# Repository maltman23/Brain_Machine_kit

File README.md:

# Brain Machine Kit  
  
A hackable Sound &amp; Light Machine kit that is easy to make,  
&nbsp;&nbsp;&nbsp;&nbsp;&nbsp;&nbsp;&nbsp;and comes pre-programmed with a really nice 14-minute meditation brainwave sequence.  
Not only that, but you get to hallucinate beautiful colors and patterns along the way...  
  
Great for **learning to solder** -- even for total beginners.  
Great for **hacking on** to play with brainwave sequences.  
Great for **Meditating, Hallucinating, and Tripping Out!**  
  
## The New Brain Machine Kit  

This new version of the Brain Machine kit functions exactly like the other versions.  
It comes pre-programmed with the same really nice meditation sequence.  
The main differences between the new Brain Machine kit and the old one are -- the new one:  
* Has a new PC Board that is much easier to solder together.  
* Uses a small Arduino Nano board, so it is much easier to re-program and hack on.  
* Can be easily re-programmed with other available Brainwave sequences.  
* The Sketch has even more comments in it than the old firmware, making it easy to modify, and great to learn from, if you like.  
* Has the ability to easily add Gama waves to a Brainwave sequence.  
* Has the ability to add alternate blinking LEDs (left/right), instead of both always blinking On/Off simultaneously.
* Runs on one AAA battery, so it is lightweight and more comfortable to wear and use.
* It can easily be re-programmed with new brainwave sequences, such as the Gamma sequence Arduino sketch (included in this repository).  
  
## Meditation sequence  
  
**The Brain Machine comes pre-programmed with a brainwave sequence for a nice 14-minute long Meditation.**  
The sequence starts with lots of Beta (awake / conscious), which is where most people will be when they begin.  
Then Alpha waves (dreamy / trancy) are added, to connect with subconscious Theta that will be coming up.  
Then the Beta is reduced (for less conscious, making it easier to be move more into a trance).  
Then some Theta (more subconscious) is added, and in the middle, there are some pulses of Delta (creativity).  
Then the sequence is reversed, to come back up, nice and refreshed.  
  
The Meditation Arduino sketch is included in this repository.  
  
## Gamma sequence  
  
[Early research over the last few years at MIT](https://picower.mit.edu/news/40-hz-vibrations-reduce-alzheimers-pathology-symptoms-mouse-models) 
and other research labs shows that "plaque" (which is one cause of Alzheimer's pathology) is reduced in mice. 
Studies are ongoing for helping humans with Alzheimer's pathology.  
40 Hz Gamma stimulation may also be [helpful for "chemo brain fog"](https://picower.mit.edu/news/noninvasive-treatment-chemo-brain).  
There may also be some benefit to people with CFS/ME, or people with "brain fog" from long Covid.  
  
A Gamma Arduino sketch is included in this repository.  It plays Gamma waves (40.0 Hz) for one hour.  
    
## Brief History of the Project  
  
The Brain Machine was originally a project I created by hacking the Adafruit MiniPOV3 kit, 
which was a really cool kit, but is no longer available.  
https://www.adafruit.com/product/20  

This was in 2007, before Arduino was popular, and I used the MiniPOV3 kit as a platform for many interesting projects.  
I used these intriguing projects to make it fun and easy to teach total beginners of all ages how to solder at my workshops all over the world.  

The Brain Machine was one of these projects -- and it was popular.  
  
I wrote up the project for MAKE Magazine, issue #10, in 2007:  
https://makezine.com/article/home/fun-games/the-brain-machine/  

After giving countless well-attended soldering workshops where Brain Machines, with the MiniPOV3 hack, 
were very popular amongst participants, 
in 2010 I got together with **Limor Fried ("Ladyada")** (who founded Adafruit Industries), to create a Brain Machine kit.  
This kit was popular for quite a number of years.  Although it is no longer available, the cool webpage for it is still up:  
https://www.adafruit.com/product/287  

In 2011, after Arduino became quite popular for making it much easier to make just about anything with microcontrollers, 
**Chris Sparnicht ("Laughter On Water")**, created an Arduino version of the Brain Machine, based on my original project.  
https://github.com/LaughterOnWater/Arduino-Brain-Machine  
Many thanks, Chris!  
  
**This year (2025) I decided to create a new, much easier to make version of the kit I made with Limor.**  
**The result is the project in this GitHub repository, with all documentation given.**  
  
## More Background of the Brain Machine  
  
It has been known since people started recording brainwaves (with an EEG) in the 1920s, that if you blink lights at brainwave frequencies, when a person watches the blinking lights (with their eyes closed), for most people, their brain will synchronize to the external brainwave frequencies.  (This is called "entrainment".)  And people subjectively say that they feel similarly as if their brain were generating those brainwave frequency on their own (for instance: a state of meditation).  One interesting (and popular) side effect is that people hallucinate beautiful colors and patterns while enjoying the state they are in.  
  
People started creating devices to generate brainwave frequencies as early as the 1950s.  Here is one example -- Brion Gysin's Dreammachine:  
https://en.wikipedia.org/wiki/Dreamachine  

Later people added sound, in the form of **"binaural beats"**.  
When there are two different pitches generated in a physical space, the difference in frequency between two pitches causes a physical "beat frequency" which everyone can hear.  
If instead, the two different pitches are presented separately to each ear, 
the difference in the two pitches is (oddly) perceived inside most peoples' brains 
as an imaginary beat frequency, which is called a "binaural beat".  
  
In the 1970s, when microcontrollers started to become affordable, people started making commercial devices that created a sequence of brainwave frequencies, presented with blinking lights (in front of glasses) and binaural beats (with headphones). These devices were called **"Sound & Light Machines".**  They were somewhat popular for some people, but also kind of expensive -- several hundred US dollars.  
  
In the early 1990s I created my own Sound & Light Machine, using an inexpensive microcontroller that was available. 
I have been meditating since I was 13 years old, and it became an important part of my well-being and my life. 
I was at a university where I volunteered as a subject for brainwave studies. 
While there I learned that you can record brainwaves and watch as people go into and out of a meditative state (and other states, such as sleep). 
I thought it would be cool to make a device that played those frequencies back 
through LEDs and binaural beats through headphones -- 
using a sequence of brainwave frequencies that were recorded from me going into and out of a nice 15-minute meditation.  The total cost was about US $5. 
I thought that others would like to be able to easily meditate by wearing and using my Sound & Light Machine 
-- especially if I promised them that they would hallucinate beautiful colors and patterns along the way. 
I considered manufacturing and selling them.  But, I was too busy at the time.  
  
Then, over 10 years later, after the first Maker Faire in 2006, after meeting Limor Fried, and seeing her MiniPOV3 kit, 
I thought it would be fun to use her kit as a platform to make it easy for total beginners to learn soldering, 
and to make several projects that I developed using the MiniPOV3 kit -- including what I now called the "Brain Machine".
  
As stated earlier, this turned into the Brain Machine kit that I created with Limor.  It also inspired Chris "Laughter On Water" to make his Arduino version.  And, many years later, I'm now making a new, Arduino-based Brain Machine kit.  
  
## How the Binaural Beats are Generated  

To create the binaural beat frequencies that we desire, 
we choose a central pitch, and generate pitches for each ear, as needed (using the Arduino Tone library), 
which are half of the desired difference higher and lower from the central pitch. 
If we choose a central pitch of 200 Hz, 
we can generate the following pitches for each ear 
to create the desired binaural beat for our brains to synch up with (entrain to):  
|Brainwave type   | R Ear  | L Ear  | Beat     |  
| :-------------: | ------ | ------ | -------: |
| Gama:           |  80.00 | 120.00 | 40.0 Hz  |
| Beta:           |  92.80 | 107.20 | 14.4 Hz  |
| Alpha:          |  94.45 | 105.55 | 11.1 Hz  |
| Theta:          |  97.00 | 103.00 |  6.0 Hz  |
| Delta:          |  98.90 | 101.10 |  2.2 Hz  |
  
## The Arduino Nano SuperMicro  

For this new version of the Brain Machine kit, I use the Arduino Nano SuperMicro as the controller.  
It is a little bigger than a postage stamp, and is a complete Arduino Nano.  
It also comes with 3 NeoPixel LEDs connected to Arduino Pin 2 (so to use Arduino Pin 2 you would need to unsolder the first NeoPixel).  
It's a nice little board, available on Aliexpress:  
https://www.aliexpress.com/item/1005006468917096.html  
For people interested in playing with this nice little board, I created a Blink_Test program to blink all of the LEDs on this board, as well as document how to easily use it with the free Arduino software:  
https://github.com/maltman23/ArduinoNanoSuperMini  
  
## DISCLAIMER  
  
Light and Sound Machines, such as this one, can be fun for many of us, 
but may be seriously dangerous for those prone to seizures or who are photosensitive. 
When in doubt, seek medical attention. 
You assume all liability for any damage 
done to your equipment, or to your own health, or to those whom you expose to this 
technology. Any and all notes, sketches or associated files within this repository are presented as is, with no promise or gurarantee of any particular result(s).  
  
USE AT YOUR OWN RISK.  
  
## License  
  
Creative Commons Attribution-Sharealike 4.0 International  
CC BY-SA 4.0  
  
https://creativecommons.org/licenses/by-sa/4.0/

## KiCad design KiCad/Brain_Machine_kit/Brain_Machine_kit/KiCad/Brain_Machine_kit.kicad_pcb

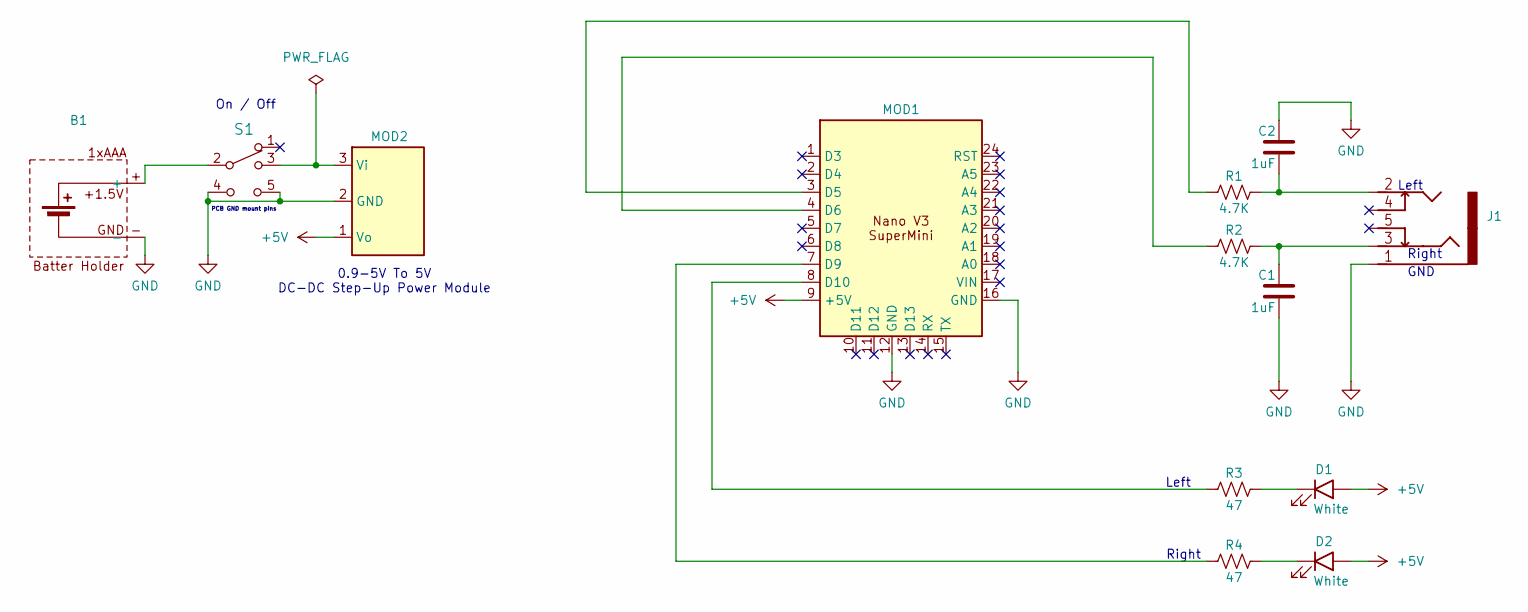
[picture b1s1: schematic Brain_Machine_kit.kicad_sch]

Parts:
B1: Battery_Holder_Keystone_2466_1xAAA_TH
C1, C2: 1uF; Cap_THT_0.5mm
D1, D2: White; LEDs_with_wires
J1: 3.5mm_CUI_SJ1-3525NG_Horizontal
MOD1: Nano_V3_SuperMini
MOD2: 0.9-5V_To_5V_DC-DC_Step-Up_Power_Module
R1, R2: 4.7K; Resistor_THT_0.25W
R3, R4: 47; Resistor_THT_0.25W
S1: SPST, 5-pin; SPST_Slide_Switch_5-pin

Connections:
+5V: D1.1 (A), D2.1 (A), MOD1.9 (+5V), MOD2.1 (Vo)
GND: B1.-, C1.2, C2.1, J1.1 (GND), MOD1.12 (GND), MOD1.16 (GND), MOD2.2 (GND), S1.4 (GND), S1.5 (GND)
unnamed: B1.+, S1.2
unnamed: D1.2 (K), R3.2
unnamed: D2.2 (K), R4.2
unnamed: C1.1, J1.3 (Ring), R2.2
unnamed: C2.2, J1.2 (Tip), R1.2
unnamed: MOD1.3 (D5), R1.1
unnamed: MOD1.4 (D6), R2.1
unnamed: MOD1.7 (D9), R4.1
unnamed: MOD1.8 (D10), R3.1
unnamed: MOD2.3 (Vi), S1.3

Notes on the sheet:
On / Off
GND
Right
0.9-5V To 5V DC-DC Step-Up Power Module
Left
PCB GND mount pins

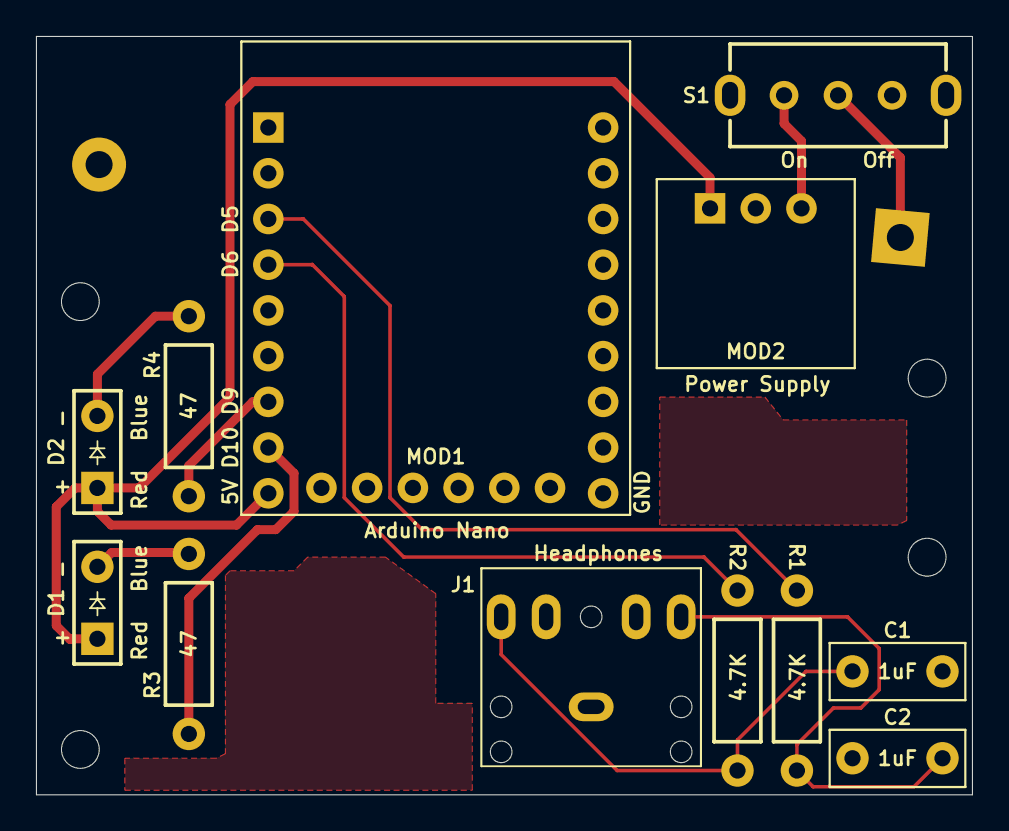
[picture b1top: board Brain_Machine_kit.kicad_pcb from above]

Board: 2 copper layers, 52.0 x 42.1 mm, 13 parts (1 on the bottom side), 12 nets.

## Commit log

2025-01-12 Update README.md
    Create a real README.md file
2025-01-13 Create BrainMachine.ino
    Add Arduino sketch for the Brain Machine kit
2025-01-13 Add KiCad files
    Add KiCad source files for Brain Machine kit
2025-01-13 add BOM and Schematic diagram
    Add BOM and Schematic diagram for Brain Machine kit
2025-01-15 Create Arduino_Nano_SuperMicro--3DModel.step
    Added 3D model from Arduino Nano SuperMicro board
2025-01-16 Update README.md
    Added link to Chris Sparnicht's Github repository (LaughterOnWater) for his Arduino Brain Machine.
2025-01-16 Update README.md
    Fix typo in Brion Gysin's name.
2025-01-16 Update README.md
    Add more licensing info for CC BY-SA
2025-01-18 update Arduino Nano 3D model on PCB
    update Arduino Nano 3D model on PCB
2025-01-27 Add Graphix, Gerbers, Test Video
    Add Graphix, Gerbers, Test Video
2025-01-27 Update README.md
    Add photos at top
2025-01-27 Update Brain_Machine_BOM.csv
    Updated BOM, including link to trippy graphix
2025-01-27 Update README.md
    spelling error
2025-01-27 Update README.md
    Change central frequency for binaural beat generation to 100.0 Hz (instead of 200.0 Hz).
2025-01-27 Update Meditation sketch, add Gamma sketch
    Minor changes to comments in the Meditation sketch.
    Added Gamma sketch: plays 1 hour of Gamma
2025-01-27 Update README.md
    Add sections for the Meditation brainwave sequence Arduino sketch and for the Gamma brainwave sequence Arduino sketch.
2025-01-27 Update README.md
    Add photo for the section on the new version of the kit, plus a line about easily re-programming.
2025-01-27 Update README.md
    Move section on this new version of the kit closer to the beginning
2025-01-28 Create BrainMachineAssembly.pdf
    Added Assembly Instructions
2025-01-30 Create BrainMachineAssemblyWorkshop.pdf
    Added Workshop slides
2025-04-02 Update Brain_Machine_BOM.csv
    fix errors in quantities of some items
